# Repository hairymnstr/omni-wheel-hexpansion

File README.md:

# Motor Hexpansion / Omni Wheel Hexpansion

This project is a "hexpansion" for the [EMF Camp Tildagon badge](https://tildagon.badge.emfcamp.org/).
It adds a motor driver, encoder reader and mounting points for an N20 motor.  The motor is mounted
straight out from the slot the hexpansion is mounted in.  By installing 3 of these hexpansions and
programming the badge appropriately you should be able to make it rotate or move in any direction
desired.

# Things you need to make a complete Omni Wheel Hexpansion

1. A Motor Hexpansion board as described in the kicad\_project folder
2. A 60mm Omni Wheel, see [my Omni Wheel repository](https://github.com/hairymnstr/OmniWheel) for a 3D printable design
3. A 110:1 geared micro metal motor with extended back shaft [COM0818 from Pimoroni](https://shop.pimoroni.com/products/micro-metal-gearmotor-extended-back-shaft?variant=39421592043603)
4. A long mounting bracket for the motor [COM0817 from Pimoroni](https://shop.pimoroni.com/products/long-micro-metal-gearmotor-bracket-pair?variant=39861109850195)
5. An encoder for the motor [PIM604 from Pimoroni](https://shop.pimoroni.com/products/micro-metal-motor-encoder?variant=39888423321683)
6. A JST-SH 6 way cable to connect the encoder/motor to the hexpansion [CAB1009 from Pimoroni](https://shop.pimoroni.com/products/jst-sh-cable-6-pin?variant=39292536455251)
7. A couple of short M2 bolts to secure the hexpansion to your badge [M2 x 5mm Torx Pan head bolt](https://www.westfieldfasteners.co.uk/Bolts_Screws_Metric/Torx_Pan_Screw_M2x5_A2_Stainless.html)

You'll need 3 of each part to make a complete hexpansion.

# Programming the hexpansion

To program a blank hexpansion I used the Raspberry Pi debug probe [(available from Pimoroni)](https://shop.pimoroni.com/products/raspberry-pi-debug-probe?variant=40511574999123).
The probe can be connected to both the SWD pins and the UART for test and debug.  The firmware
is also in this repository and can be built easily using Visual Studio Code or just by running
the Makefile provided you have an ARM embedded compiler installed.

# Hexpansion API

The hexpansion has a very simple interface, everything is controlled via I2C.

There are 2 devices presented (both in software on the STM32):

* 0x50 is a 256 byte fake EEPROM which has a valid "hexpansion" header identifying the board
* 0x42 has a register based control and status interface

Both devices operate in "memory" mode, i.e. they take an address then data to be read or written.
Both use single byte addressing.  Using the Micropython `readfrom_mem` and `writeto_mem` functions
will work.

There are only 2 registers defined, they can both be read and written, reading or writing any
other part of the 256 byte address space will be stored but won't make any difference to the
operation of the device.  Reads are guaranteed to be coherent so you won't get part of a register
that's updated between starting the I2C transaction and finishing it.

* Address 0, length 16 bit little endian: PWM value, a value in the range -100 to 100
* Address 2, length 16 bit little endian: Encoder position

Using the badge software you can use `machine.I2C` and `struct` to access these registers.
Note that on the Tildagon badge there are I2C buses for each hexpansion so you will need
to change the paramter to `I2C` for each slot you connect to.

This trivial example sets the speed to full reverse then prints out the current
encoder value.

    import struct
    import machine

    bus = machine.I2C(2)
    bus.writeto_mem(0x42, 0, struct.pack("<h", -100))
    print(struct.unpack("<h", bus.readfrom_mem(0x42, 2, 2))[0])

# Questions I think might be asked
## Why all the fuss about encoders?

Well originally I was planning a pen holding hexpansion as well and making a floor-turtle type
system.  To get any kind of accurate and repeatable motions I needed to know how far the wheels
were actually turning as there are variations between motors especially when under load.

## What's the point of the external MCU?

You could drive the motor driver and maybe do the encoder reading all from the MCU on the badge
itself.  But, I wanted to make sure I as catching all that encoder information on all three
motors.  To do that I decided a dedicated encoder controller would be good but couldn't find
one.  I also looked at using an I2C H-Bridge and adding an I2C EEPROM for board identification
and realised using one of the very cheap STM32G0 MCUs I could emulate an EEPROM and make an I2C
controlled motor driver and have a dedicated hardware encoder interface all in one.

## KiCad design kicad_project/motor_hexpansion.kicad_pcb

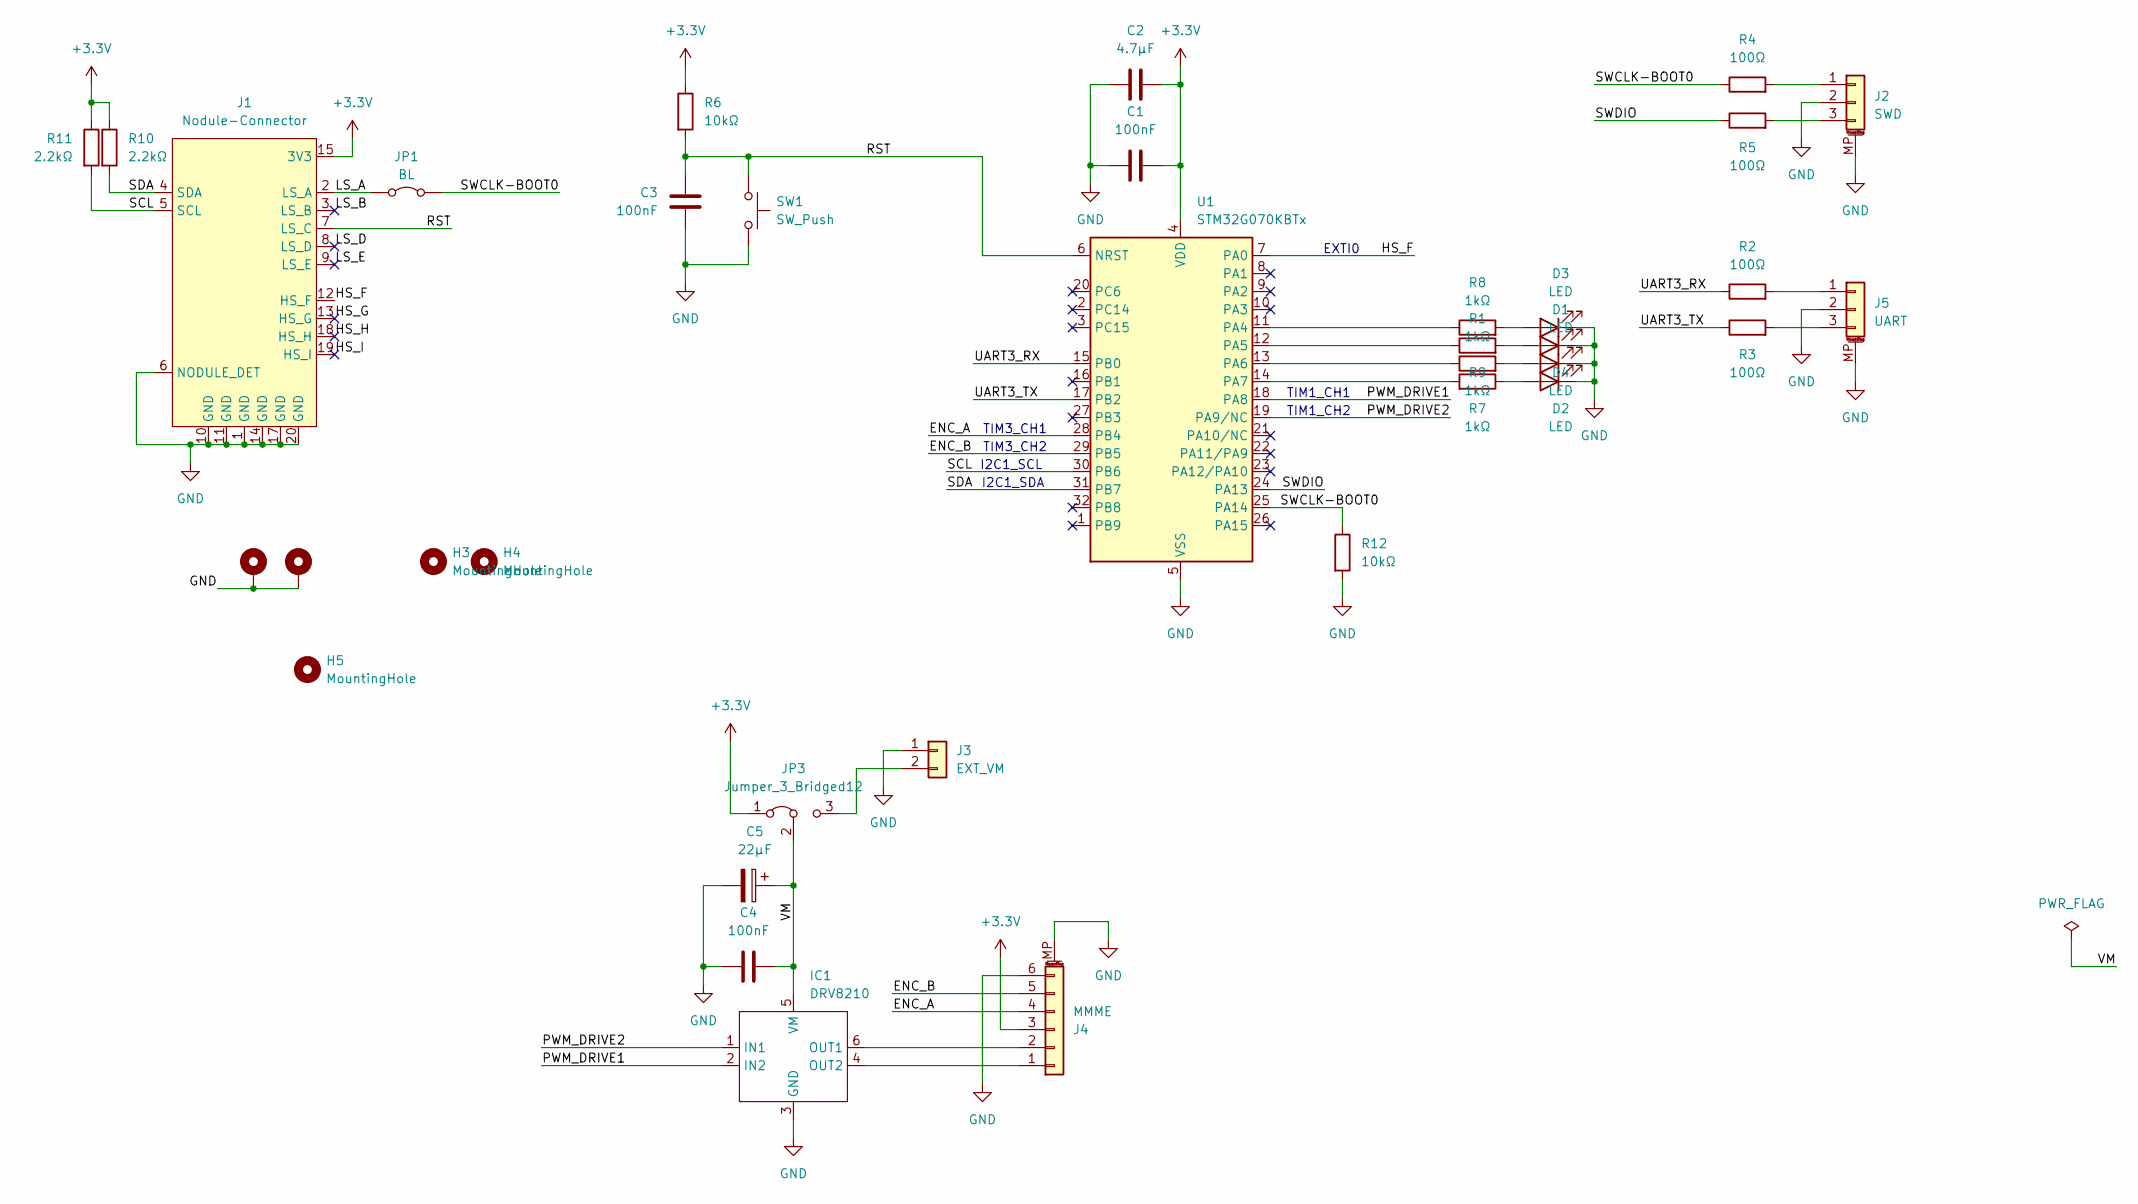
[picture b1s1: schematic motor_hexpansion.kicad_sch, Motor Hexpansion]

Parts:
C1, C3, C4: 100nF; C_0603_1608Metric
C2: 4.7µF; C_0603_1608Metric
C5: 22µF; CP_Elec_5x5.4
D1, D2, D3, D4: LED; LED_0603_1608Metric_Pad1.05x0.95mm_HandSolder
H1, H2: MountingHole_Pad; MountingHole_2.2mm_M2_Pad_Via
H3, H4: MountingHole; MountingHole_2.2mm_M2
H5: MountingHole; dclogo
IC1: DRV8210; SOT-563
J1: Nodule-Connector; nodule-edge-connector
J2: SWD; JST_SH_SM03B-SRSS-TB_1x03-1MP_P1.00mm_Horizontal
J3: EXT_VM; Molex_KK-254_AE-6410-02A_1x02_P2.54mm_Vertical
J4: MMME; JST_SH_SM06B-SRSS-TB_1x06-1MP_P1.00mm_Horizontal
J5: UART; JST_SH_SM03B-SRSS-TB_1x03-1MP_P1.00mm_Horizontal
JP1: BL; SolderJumper-2_P1.3mm_Bridged_Pad1.0x1.5mm
JP3: Jumper_3_Bridged12; SolderJumper-3_P1.3mm_Bridged2Bar12_Pad1.0x1.5mm_NumberLabe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
R1, R7, R8, R9: 1kΩ; R_0603_1608Metric
R2, R3, R4, R5: 100Ω; R_0603_1608Metric
R6, R12: 10kΩ; R_0603_1608Metric
R10, R11: 2.2kΩ; R_0603_1608Metric
SW1: SW_Push; Panasonic_EVQPUL_EVQPUC
U1: STM32G070KBTx; LQFP-32_7x7mm_P0.8mm

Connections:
+3.3V: C1.2, C2.2, J1.15 (3V3), J1.16 (3V3), J4.3, JP3.1 (A), R6.1, R10.1, R11.1, U1.4 (VDD)
/ENC_A: J4.4, U1.28 (PB4)
/ENC_B: J4.5, U1.29 (PB5)
/HS_F: J1.12 (HS_F), U1.7 (PA0)
/HS_G: J1.13 (HS_G)
/HS_H: J1.18 (HS_H)
/HS_I: J1.19 (HS_I)
/LS_A: J1.2 (LS_A), JP1.1 (A)
/LS_B: J1.3 (LS_B)
/LS_D: J1.8 (LS_D)
/LS_E: J1.9 (LS_E)
/PWM_DRIVE1: IC1.2 (IN2), U1.18 (PA8)
/PWM_DRIVE2: IC1.1 (IN1), U1.19 (PA9/NC)
/RST: C3.1, J1.7 (LS_C), R6.2, SW1.1, U1.6 (NRST)
/SCL: J1.5 (SCL), R11.2, U1.30 (PB6)
/SDA: J1.4 (SDA), R10.2, U1.31 (PB7)
/SWCLK-BOOT0: JP1.2 (B), R4.1, R12.1, U1.25 (PA14)
/SWDIO: R5.1, U1.24 (PA13)
/UART3_RX: R2.1, U1.15 (PB0)
/UART3_TX: R3.1, U1.17 (PB2)
/VM: C4.2, C5.1, IC1.5 (VM), JP3.2 (C)
GND: C1.1, C2.1, C3.2, C4.1, C5.2, D1.1 (K), D2.1 (K), D3.1 (K), D4.1 (K), H1.1, H2.1, IC1.3 (GND), J1.1 (GND), J1.6 (NODULE_DET), J1.10 (GND), J1.11 (GND), J1.14 (GND), J1.17 (GND), J1.20 (GND), J2.2, J2.MP (MountPin), J3.1, J4.6, J4.MP (MountPin), J5.2, J5.MP (MountPin), R12.2, SW1.2, U1.5 (VSS)
unnamed: D1.2 (A), R1.2
unnamed: D2.2 (A), R7.1
unnamed: D3.2 (A), R8.2
unnamed: D4.2 (A), R9.2
unnamed: IC1.6 (OUT1), J4.2
unnamed: IC1.4 (OUT2), J4.1
unnamed: J2.1, R4.2
unnamed: J2.3, R5.2
unnamed: J3.2, JP3.3 (B)
unnamed: J5.1, R2.2
unnamed: J5.3, R3.2
unnamed: R8.1, U1.11 (PA4)
unnamed: R9.1, U1.12 (PA5)
unnamed: R1.1, U1.13 (PA6)
unnamed: R7.2, U1.14 (PA7)

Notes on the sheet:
TIM1_CH2
EXTI0
I2C1_SDA
TIM1_CH1
I2C1_SCL
TIM3_CH1
TIM3_CH2

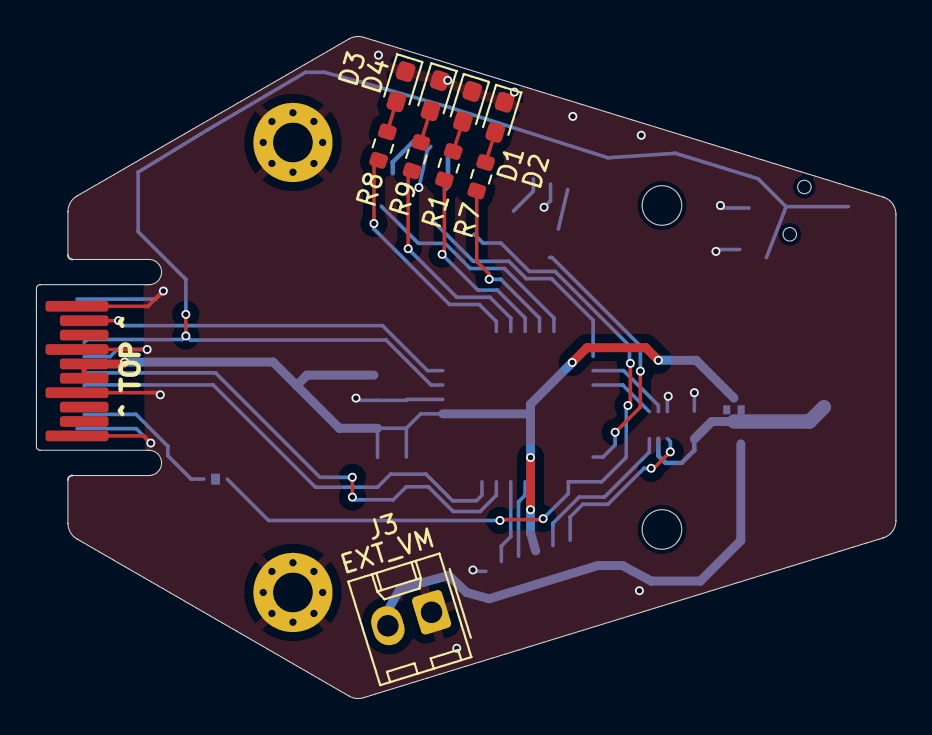
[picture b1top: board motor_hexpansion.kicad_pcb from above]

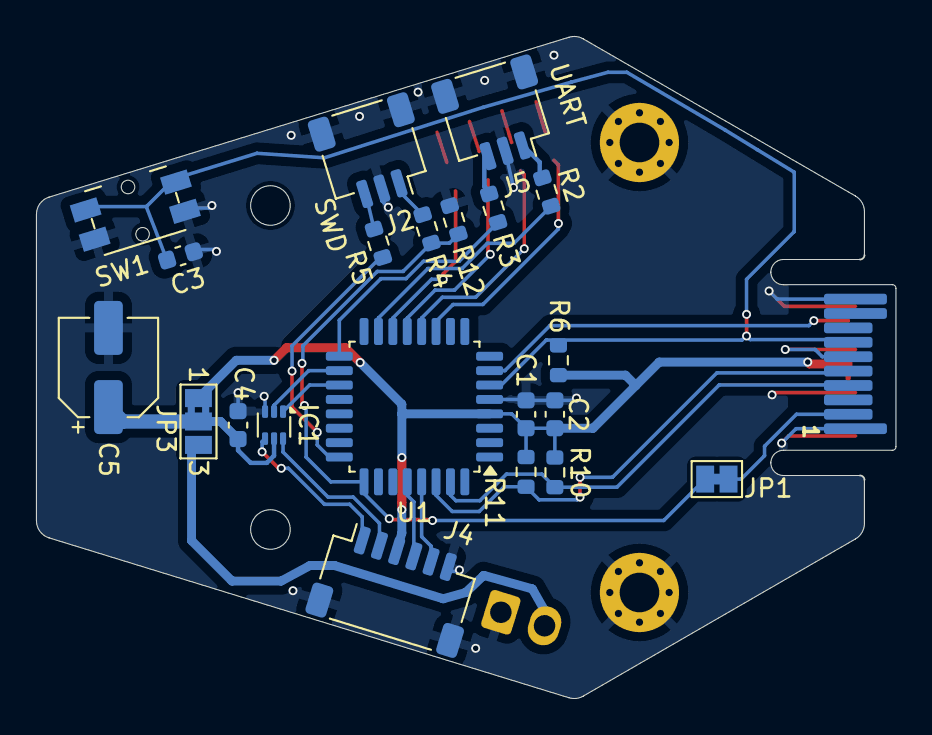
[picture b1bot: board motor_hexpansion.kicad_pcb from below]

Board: 2 copper layers, 47.7 x 36.7 mm, 35 parts (21 on the bottom side), 31 nets.

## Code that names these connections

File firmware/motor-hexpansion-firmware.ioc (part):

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Mcu.Name=STM32G070KBTx
Mcu.Package=LQFP32
Mcu.UserName=STM32G070KBTx
PA0.Signal=GPXTI0
PA13.Mode=Serial_Wire
PA13.Signal=SYS_SWDIO
PA14-BOOT0.Mode=Serial_Wire
PA14-BOOT0.Signal=SYS_SWCLK
PA4.GPIOParameters=GPIO_Label
PA4.GPIO_Label=LED0
PA4.Signal=GPIO_Output
PA5.GPIOParameters=GPIO_Label
PA5.GPIO_Label=LED1
PA5.Signal=GPIO_Output
PA6.GPIOParameters=GPIO_Label
PA6.GPIO_Label=LED2
PA6.Signal=GPIO_Output
PA7.GPIOParameters=GPIO_Label
PA7.GPIO_Label=LED3
PA7.Signal=GPIO_Output
PA8.Signal=S_TIM1_CH1
PA9.Signal=S_TIM1_CH2
PB0.Mode=Asynchronous
PB0.Signal=USART3_RX
PB2.Mode=Asynchronous
PB2.Signal=USART3_TX
PB4.Signal=S_TIM3_CH1
PB5.Signal=S_TIM3_CH2
PB6.Mode=I2C
PB6.Signal=I2C1_SCL
PB7.Mode=I2C
PB7.Signal=I2C1_SDA
RCC.HSE_VALUE=8000000
RCC.SYSCLKFreq_VALUE=64000000
RCC.SYSCLKSource=RCC_SYSCLKSOURCE_PLLCLK
board=custom

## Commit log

2024-05-25 Adding files to version control for sharing
2024-05-25 Adding the project firmware as well
2024-05-25 Adding some documentation
2024-05-26 Made the I2C interface work. Needs more eeprom work
2024-05-26 Valid fake eeprom contents
2024-05-26 Updated docs with some programming guidance
